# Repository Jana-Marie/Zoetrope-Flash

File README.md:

# Zoetrope-Flash

Zoetrope-Flash is a flash built for machine vision. It is based on the LED pcb of Enlightened Otter.

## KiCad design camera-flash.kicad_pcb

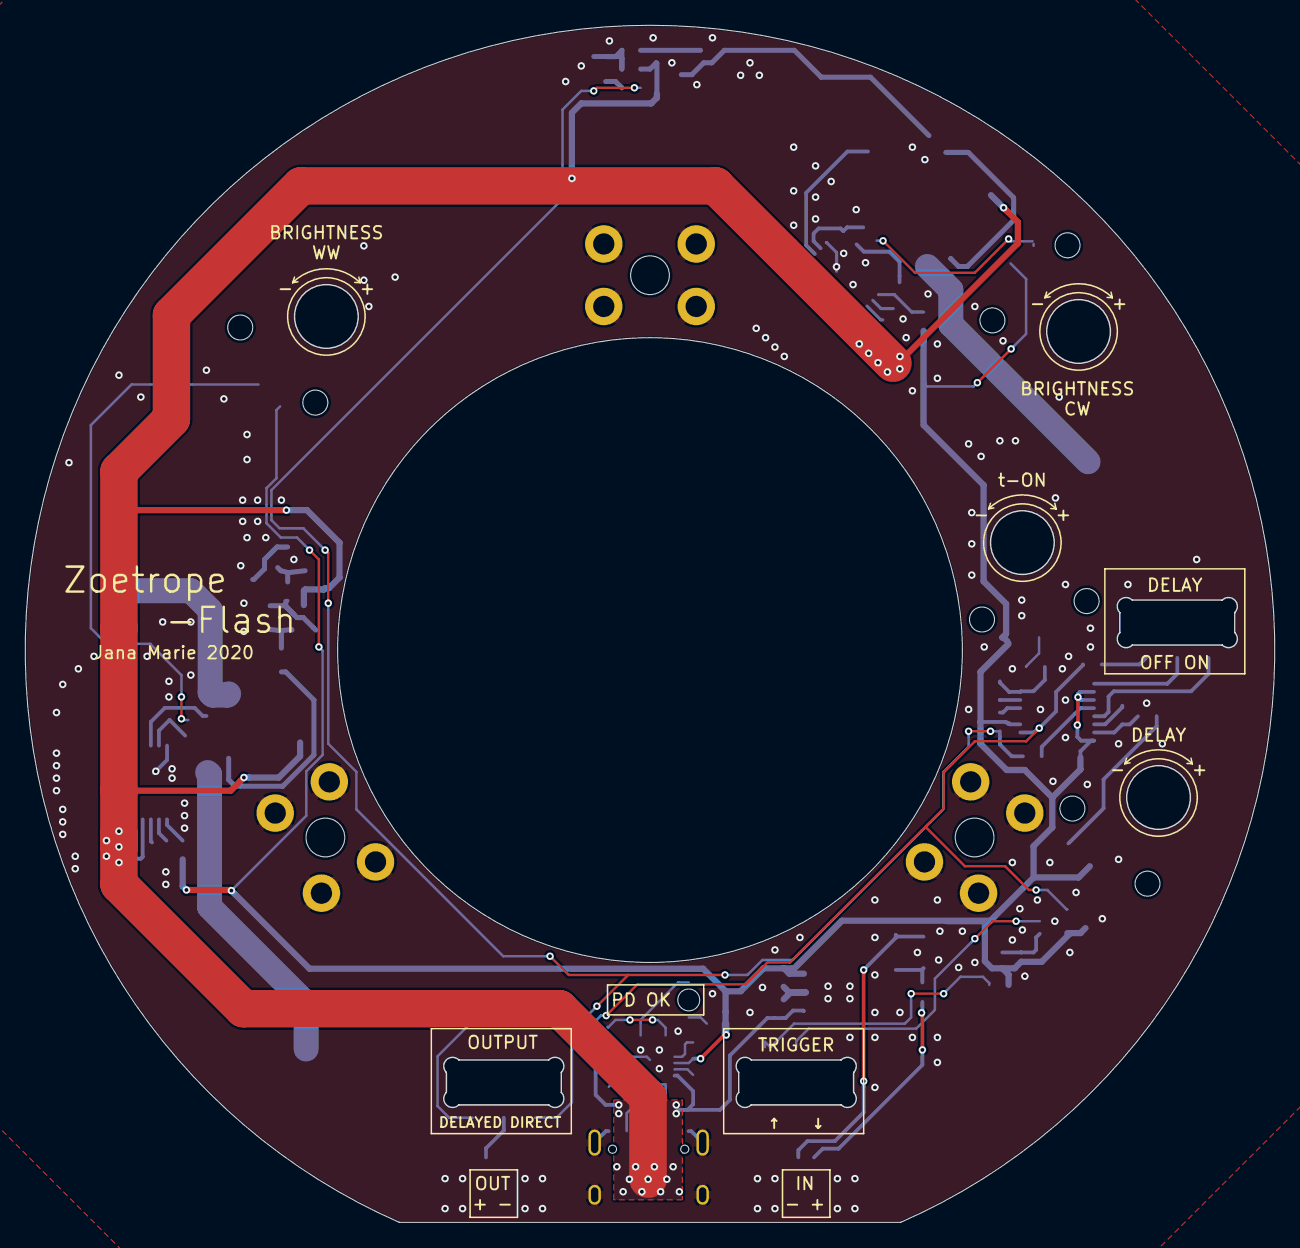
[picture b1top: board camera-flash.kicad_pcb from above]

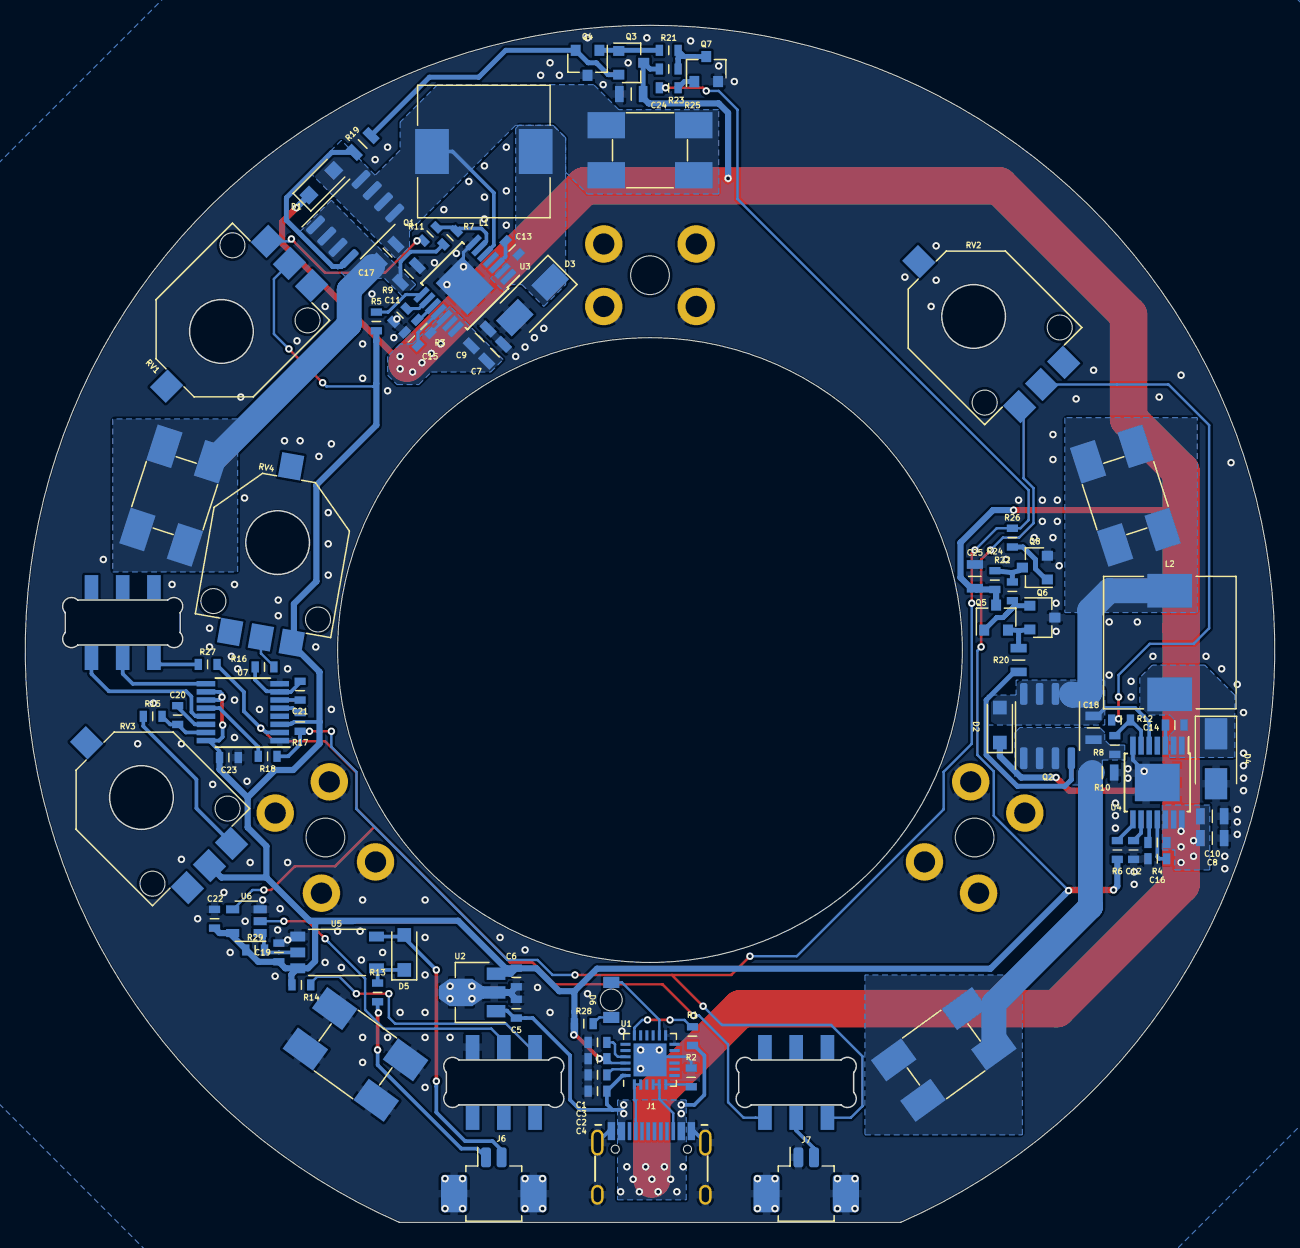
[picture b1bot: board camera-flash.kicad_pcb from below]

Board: 2 copper layers, 99.9 x 95.7 mm, 95 parts (92 on the bottom side), 61 nets.

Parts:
C1, C2, C5, C6: 1uF; C_0603
C3, C4, C11, C12, C15, C16, C19, C22, C23: 100nF; C_0603
C7, C8, C9, C10, C24, C25: 10uF; C_0805
C13, C14: 22nF; C_0603
C17, C18: DNP; C_0805
C20, C21: 470n; C_0603
D1, D2, D5: D; D_SOD-123F
D3, D4: D_Schottky; D_SMA
D6: LED; LED_Reverse
J1: USB; USB-C 16Pin
J2: LED_WW_A; Screw_Terminal_6x6x6mm
J3: LED_WW_C; Screw_Terminal_6x6x6mm
J4: LED_CW_A; Screw_Terminal_6x6x6mm
J5: LED_CW_C; Screw_Terminal_6x6x6mm
J6: IN; Molex_PicoBlade_53261-0271_1x02-1MP_P1.25mm_Horizontal
J7: OUT; Molex_PicoBlade_53261-0271_1x02-1MP_P1.25mm_Horizontal
J8, J9, J10: CAM; flash_terminal
J11: GND; Screw_Terminal_6x6x6mm
L1, L2: 47uH; L_10.4x10.4_H4.8
Q1, Q2: ONSC-NMOS-8_E; SO-8_3.9x4.9mm_P1.27mm
Q3, Q5, Q7, Q8: BC847; SOT-23
Q4, Q6: BC857; SOT-23
R1, R2, R21, R22, R23, R24, R25, R26, R28: 3k3; R_0603
R3, R4: 150k; R_0603
R5, R6, R14, R27, R29: 10k; R_0603
R7, R8: 1k; R_0603
R9, R10: 0.4; R_0805
R11, R12: 15k; R_0603
R13, R15, R16: 100; R_0603
R17: 0; R_0603
R18: DNP; R_0603
R19, R20: 20; R_0805
RV1, RV2, RV3, RV4: 100k; SV01A103AEA01R00
SW1: out; 2P2T_R
SW2: invert; 2P2T_R
SW3: no_delay; 2P2T_R
U1: STUSB4500; QFN-24-1EP_4x4mm_P0.5mm_EP2.7x2.7mm
U2: AP2204R-3.3; SOT-89-3
U3, U4: lm3406; TSSOP-14-1EP_4.4x5mm_P0.65mm
U5: TLP2366; SO6-5
U6: 74LVC1G86; SOT-23-5
U7: 74HCT123; TSSOP-16_4.4x5mm_P0.65mm

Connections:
+3V3: C3.2, C6.2, C19.1, C22.1, C23.1, R5.1, R6.1, R14.2, R28.2, R29.1, RV1.2, RV2.1, RV3.2, RV4.3, U1.22, U2.3, U5.6, U6.5, U7.3, U7.10, U7.11, U7.16
CC1: J1.A5, U1.1, U1.2
CC2: J1.B5, U1.4, U1.5
CW_DIM: R8.1, R12.2, U4.6
GND: C1.1, C2.1, C3.1, C4.1, C5.1, C6.1, C7.2, C8.2, C9.2, C10.2, C11.2, C12.2, C15.2, C16.2, C19.2, C22.2, C23.2, C24.2, C25.2, D3.2, D4.2, J1.A1, J1.A12, J1.B1, J1.B12, J1.S1, J6.MP, J7.1, J7.MP, J8.1, J9.1, J10.1, J11.1, Q4.3, Q6.3, Q7.2, Q8.2, R2.2, R9.2, R10.2, SW2.1, U1.10, U1.12, U1.13, U1.25, U2.2, U3.7, U3.15, U4.7, U4.15, U5.4, U6.3, U7.1, U7.8
IS_PD_OK: D6.1, U1.14
unnamed: C1.2, U1.21
unnamed: C2.2, U1.23
unnamed: C11.1, U3.9
unnamed: C12.1, U4.9
unnamed: C13.1, D3.1, L1.1, U3.1, U3.2
unnamed: C13.2, U3.3
unnamed: C14.1, D4.1, L2.1, U4.1, U4.2
unnamed: C14.2, U4.3
unnamed: C15.1, U3.11
unnamed: C16.1, U4.11
unnamed: C17.1, D1.2, J2.1, L1.2, Q1.5, Q1.6, Q1.7, Q1.8, U3.5
unnamed: C17.2, J3.1, Q1.1, Q1.2, Q1.3, R7.2, R9.1
unnamed: C18.1, D2.2, J4.1, L2.2, Q2.5, Q2.6, Q2.7, Q2.8, U4.5
unnamed: C18.2, J5.1, Q2.1, Q2.2, Q2.3, R8.2, R10.1
unnamed: C20.1, U7.14
unnamed: C20.2, R15.2, U7.15
unnamed: C21.1, U7.6
unnamed: C21.2, R16.2, U7.7
unnamed: D5.1, R13.1, U5.1
unnamed: D5.2, J6.2, U5.3
unnamed: D6.2, R28.1
unnamed: J6.1, R13.2
unnamed: J7.2, SW1.2
unnamed: Q1.4, R19.1
unnamed: Q2.4, R20.1
unnamed: Q3.1, Q4.1, R21.1
unnamed: Q3.2, Q4.2, R19.2
unnamed: Q5.1, Q6.1, R22.1
unnamed: Q5.2, Q6.2, R20.2
unnamed: Q7.1, R25.1
unnamed: Q7.3, R21.2, R23.2
unnamed: Q8.1, R26.1
unnamed: Q8.3, R22.2, R24.2
unnamed: R1.1, U1.18
unnamed: R2.1, U1.6
unnamed: R3.2, U3.10
unnamed: R4.2, U4.10
unnamed: R5.2, U3.8
unnamed: R6.2, U4.8
unnamed: R11.1, RV1.3
unnamed: R12.1, RV2.2
unnamed: R14.1, SW2.3
unnamed: R15.1, RV3.3
unnamed: R16.1, RV4.2
unnamed: R17.1, U7.5
unnamed: R18.2, U7.12
unnamed: R27.1, SW3.1
unnamed: R29.2, U5.5, U6.1
unnamed: SW2.2, U6.2
unnamed: SW3.2, U7.9
unnamed: SW3.3, U7.13
VBUS: C4.2, C5.2, C7.1, C8.1, C9.1, C10.1, C24.1, C25.1, D1.1, D2.1, J1.A4, J1.A9, J1.B4, J1.B9, Q3.3, Q5.3, R1.2, R3.1, R4.1, R23.1, R24.1, U1.24, U2.1, U3.12, U3.13, U3.14, U4.12, U4.13, U4.14
WW_DIM: R7.1, R11.2, U3.6
flash_in: R27.2, SW1.3, U6.4, U7.2
flash_pulse: R17.2, R18.1, R25.2, R26.2, SW1.1

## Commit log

2020-06-11 added gitignore
2020-06-11 routing 50% done"
2020-07-23 finished layout
2020-09-09 initial commit #2
2020-09-09 moved 3d files
2020-09-09 added images
2022-01-18 updated to kicad 6
2023-04-21 updated files
